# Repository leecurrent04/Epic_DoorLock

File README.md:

# EPIC Door Lock Project

## 1. 프로젝트 소개

연초고등학교 EPIC 동아리(2021~2022) 에서 교내 학생들의 자발적인 탐구 활동을 장려하기 위해 진행한 프로젝트 입니다.<br>
하드웨어 설계는 [KiCAD](https://www.kicad.org/) 를 사용하였고, 소프트웨어는 avr-gcc 컴파일러를 이용한 avr C 언어로 작성되었습니다.

<br>

## 2. 컴파일

Makefile을 이용하여 컴파일하는 경우, Makefile과 같은 위치에 `out` 폴더를 생성해야 합니다.

| 필요한 패키지 | 설명               |
| :-----------: | :----------------- |
|    avr-gcc    | 컴파일러           |
|   avr-libc    | 라이브러리         |
|   avr-size    | 메모리 사용량 확인 |
|    avrdude    | 업로더             |

<br>

### 1. in Linux

1. Set up (Debian)
    <br>
    패키지 설치는 Debian 기준으로 설명하고 있습니다. 자신의 환경에 맞추어 사용하시길 바랍니다.
    <br>

    ```console
    apt update && apt upgrade
    apt install avr-gcc avr-libc avr-size avrdude
    ```
    <br>

2. Download source code
    <br>
    ```console
    git clone https://github.com/leecurrent04/Epic_DoorLock
    cd ./Epic_DoorLock/ver3/code/avr/
    ```
    <br>

3. Set admin card
    <br>
    [main.c](https://github.com/leecurrent04/Epic_DoorLock/blob/main/ver3/code/avr/main.c) 파일의 16, 17줄을 편집하여 관리자 카드를 등록합니다.<br>
    RFID 카드의 4byte UID 코드를 1byte씩 기입합니다. 카드의 UID 코드는 [[NFC Tools - Google Play]](https://play.google.com/store/apps/details?id=com.wakdev.wdnfc&hl=en) 프로그램을 통하여 알 수 있습니다. (프로그램내 시리얼 번호 확인)<br>
    반드시 등록한 관리자 카드의 갯수에 맞게 `cardAdmin_Num` 값을 변경해주어야 합니다.
    <br>
    ```c
    #define cardAdmin_Num 2
    uint8_t cardAdmin_UID[cardAdmin_Num][4] = {
            {0x12, 0x34, 0x56, 0x78},
            {0x0A, 0x0B, 0x0C, 0x0D}
    };
    ```
    <br>

4. Complile
    <br>
    변경 사항을 저장한 후 아래 명령어를 이용하여 코드를 컴파일 합니다.
    <br>
    ```console
    mkdir out
    make all
    ```
    <br>또는 다음과 같은 명령어를 사용할 수 있습니다.<br>

    ```console
	avr-gcc -Wall -mmcu=atmega168p -Os main.c ./lib/* -o ./out/output.o
	avr-objcopy -j .text -j .data -O ihex ./out/output.o ./out/main.hex
    ```
    <br>

5. Upload
    <br>
    [Makefile](https://github.com/leecurrent04/Epic_DoorLock/blob/main/ver3/code/avr/Makefile) 의 2, 4, 5번째 줄을 환경에 맞게 편집합니다.<br>

    ```makefile
    PORT=/dev/ttyUSB0       # SET YOUR PORT
    OBJ_FILES=./lib/*
    BaudRate=115200         # SET BuadRate
    PROGRAMMER=arduino      # SET Programmer
    ```

    <br>아래의 명령어를 터미널에 입력하여 업로드 합니다.<br>

    ```console
    make flash
    ```

    <br>USBtinyISP를 사용하는 경우(권장), 다음의 명령어를 터미널에 입력하면 됩니다.<br>

    ```console
	avrdude -v -p m168p -c usbtiny -U flash:w:./out/main.hex:i
    ```

    <br><br>

### 2. Windows & Mac

[Microchip AVR GCC Compiler](https://www.microchip.com/en-us/tools-resources/develop/microchip-studio/gcc-compilers) 를 사용하여 Linux와 같은 과정을 따르거나, ATMEL Studio를 사용하십시오. <br>
자세한 과정은 『아트멜 스튜디오와 아두이노로 배우는 ATmega328 프로그래밍(허경용)』 도서를 참고하십시오.<br>
(이 프로젝트는 ATmega168p을 사용하였으므로, 업로드 과정에서 유의)
<br><br>

## 4. 참고 라이브러리

RFID 관련 AVR 라이브러리 : https://github.com/asif-mahmud/MIFARE-RFID-with-AVR

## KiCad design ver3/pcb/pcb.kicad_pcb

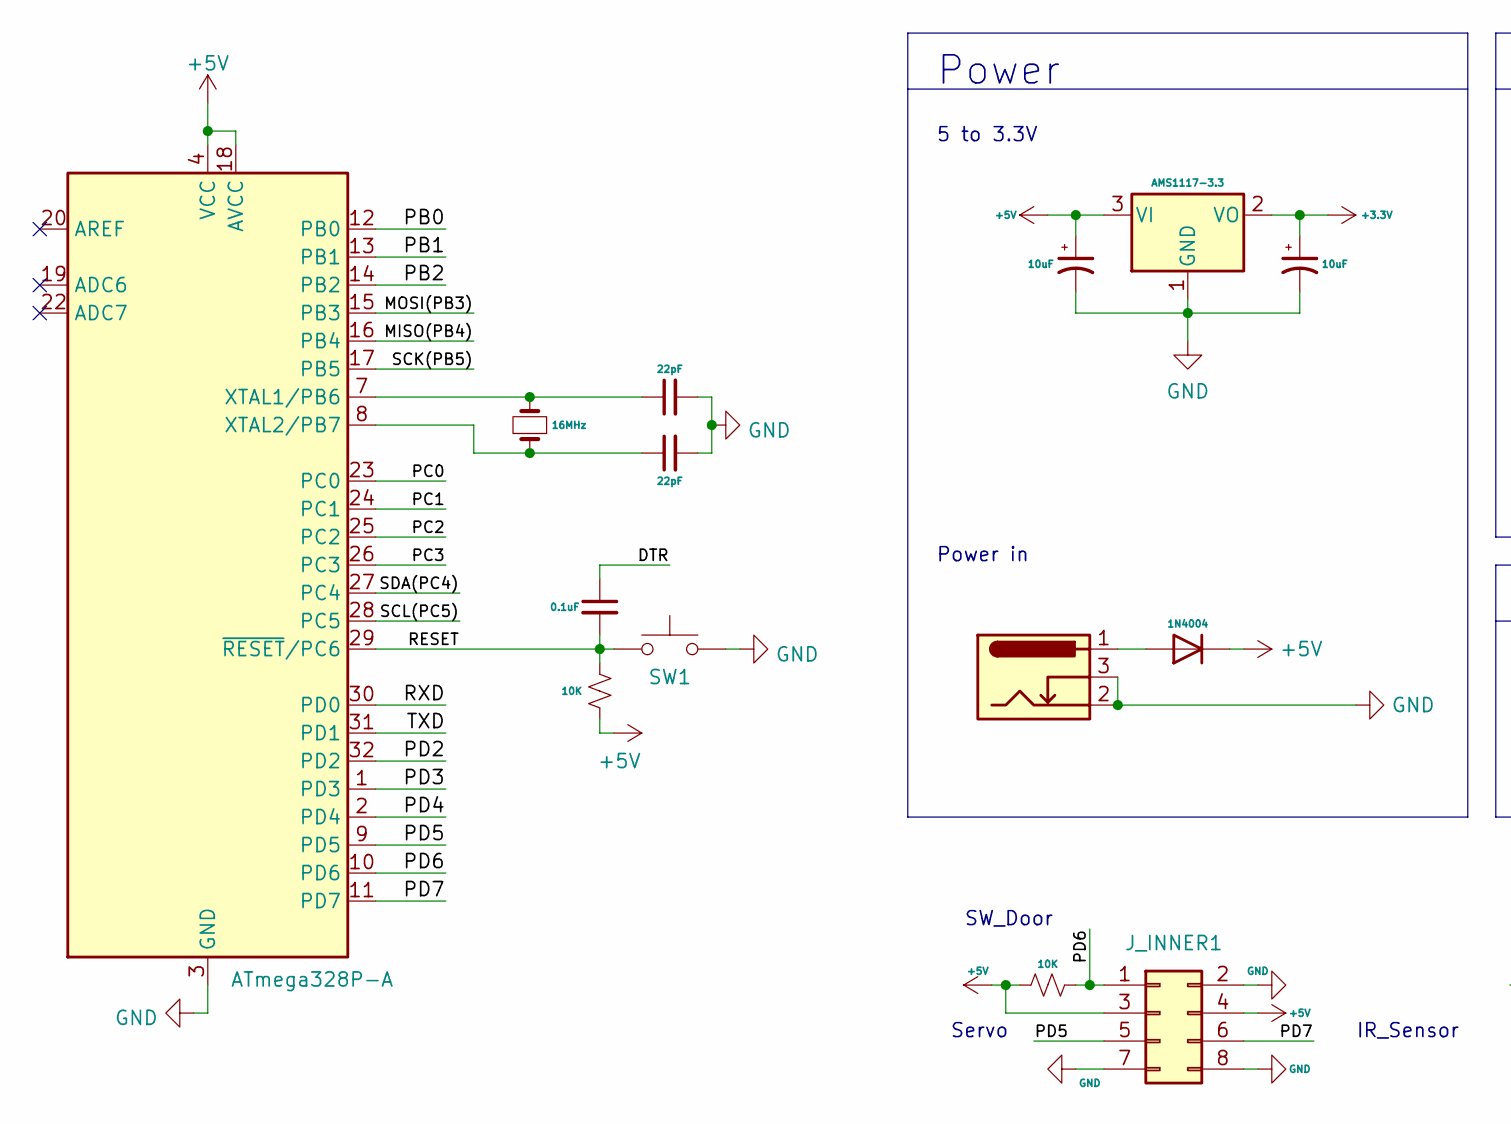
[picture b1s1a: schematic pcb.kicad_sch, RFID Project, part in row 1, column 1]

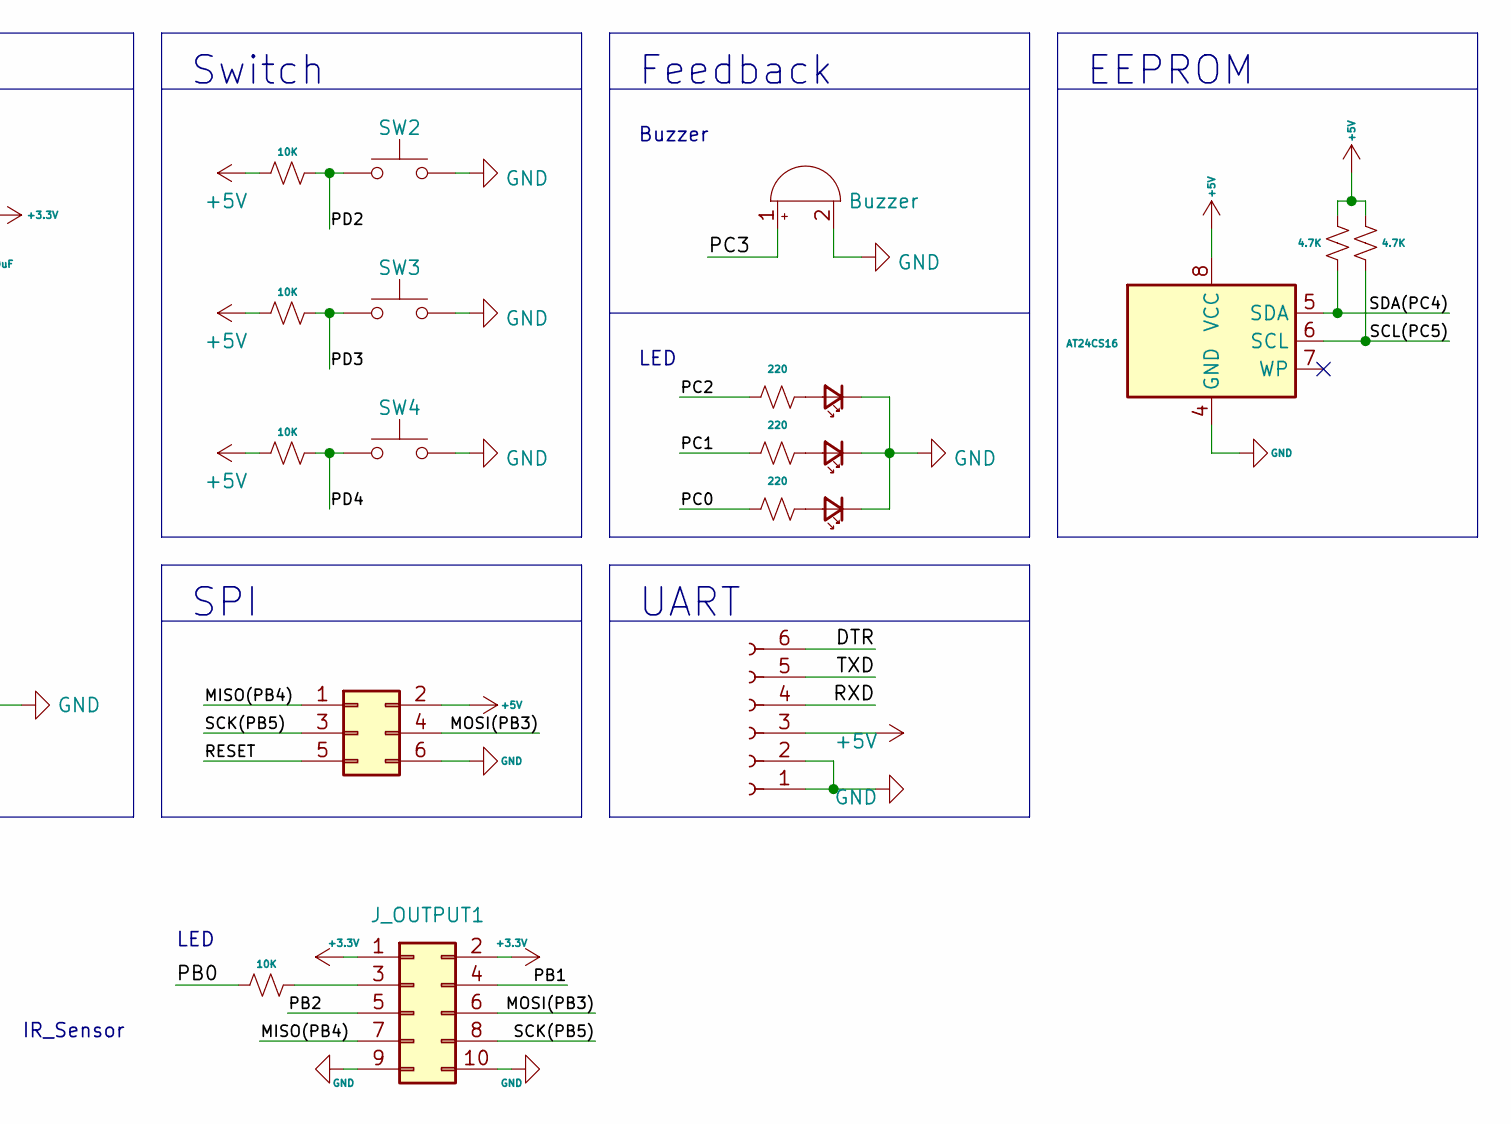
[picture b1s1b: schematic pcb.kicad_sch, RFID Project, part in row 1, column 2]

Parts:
BZ1: Buzzer; FQ-014[Buzzer]
C1: 0.1uF; C_0603_1608Metric
C2, C3: 22pF; C_0603_1608Metric
C4, C5: 10uF; CP_EIA-3216-10_Kemet-I
D1: 1N4004; D_SMA
D2, D3, D4: LED_Small; LED_0603_1608Metric
J_INNER1: Conn_02x04_Odd_Even; PinHeader_2x04_P2.54mm_Vertical
J_OUTPUT1: Conn_02x05_Odd_Even; PinHeader_2x05_P2.54mm_Vertical
J_SPI1: Conn_02x03_Odd_Even; PinHeader_2x03_P2.54mm_Vertical
J_UART1: Conn_01x06_Female; PinHeader_1x06_P2.54mm_Vertical
POWER_JACK1: 5.5pi; BarrelJack_Horizontal
R1, R2, R3, R4, R5, R6: 10K; R_0603_1608Metric
R7, R8, R9: 220; R_0603_1608Metric
R10, R11: 4.7K; R_0603_1608Metric
SW1: SW_Push; PinHeader_1x02_P2.54mm_Vertical
SW2: SW_Push; SW_PUSH-12mm
SW3, SW4: SW_Push; SW_PUSH_6mm_H5mm
U1: ATmega328P-A; TQFP-32_7x7mm_P0.8mm
U2: AMS1117-3.3; SOT-223-3_TabPin2
U3: AT24CS16; DIP-8_W7.62mm_Socket_LongPads
Y1: 16MHz; Crystal_HC49-4H_Vertical

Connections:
+3V3: C5.1, J_OUTPUT1.1, J_OUTPUT1.2, U2.2 (VO)
+5V: C4.1, D1.1 (K), J_INNER1.3, J_INNER1.4, J_SPI1.2, J_UART1.3, R1.1, R2.2, R4.1, R5.1, R6.1, R10.1, R11.1, U1.4 (VCC), U1.6 (VCC), U1.18 (AVCC), U2.3 (VI), U3.8 (VCC)
/DTR: C1.1, J_UART1.6
/MISO(PB4): J_OUTPUT1.7, J_SPI1.1, U1.16 (PB4)
/MOSI(PB3): J_OUTPUT1.6, J_SPI1.4, U1.15 (PB3)
/PB0: R3.1, U1.12 (PB0)
/PB1: J_OUTPUT1.4, U1.13 (PB1)
/PB2: J_OUTPUT1.5, U1.14 (PB2)
/PC0: R9.1, U1.23 (PC0)
/PC1: R8.1, U1.24 (PC1)
/PC2: R7.1, U1.25 (PC2)
/PC3: BZ1.1 (-), U1.26 (PC3)
/PD2: R4.2, SW2.1, U1.32 (PD2)
/PD3: R5.2, SW3.1, U1.1 (PD3)
/PD4: R6.2, SW4.1, U1.2 (PD4)
/PD5: J_INNER1.5, U1.9 (PD5)
/PD6: J_INNER1.1, R2.1, U1.10 (PD6)
/PD7: J_INNER1.6, U1.11 (PD7)
/RESET: C1.2, J_SPI1.5, R1.2, SW1.1, U1.29 (~RESET/PC6)
/RXD: J_UART1.4, U1.30 (PD0)
/SCK(PB5): J_OUTPUT1.8, J_SPI1.3, U1.17 (PB5)
/SCL(PC5): R11.2, U1.28 (PC5), U3.6 (SCL)
/SDA(PC4): R10.2, U1.27 (PC4), U3.5 (SDA)
/TXD: J_UART1.5, U1.31 (PD1)
GND: BZ1.2 (+), C2.2, C3.2, C4.2, C5.2, D2.1 (K), D3.1 (K), D4.1 (K), J_INNER1.2, J_INNER1.7, J_INNER1.8, J_OUTPUT1.9, J_OUTPUT1.10, J_SPI1.6, J_UART1.1, J_UART1.2, POWER_JACK1.2, POWER_JACK1.3, SW1.2, SW2.2, SW3.2, SW4.2, U1.3 (GND), U1.5 (GND), U1.21 (GND), U2.1 (GND), U3.4 (GND)
unnamed: C2.1, U1.7 (XTAL1/PB6), Y1.2
unnamed: C3.1, U1.8 (XTAL2/PB7), Y1.1
unnamed: D1.2 (A), POWER_JACK1.1
unnamed: D2.2 (A), R7.2
unnamed: D3.2 (A), R8.2
unnamed: D4.2 (A), R9.2
unnamed: J_OUTPUT1.3, R3.2

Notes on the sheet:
Feedback
Power in
Power
Servo
UART
Buzzer
IR_Sensor
LED
SW_Door
SPI
5 to 3.3V
EEPROM
Switch

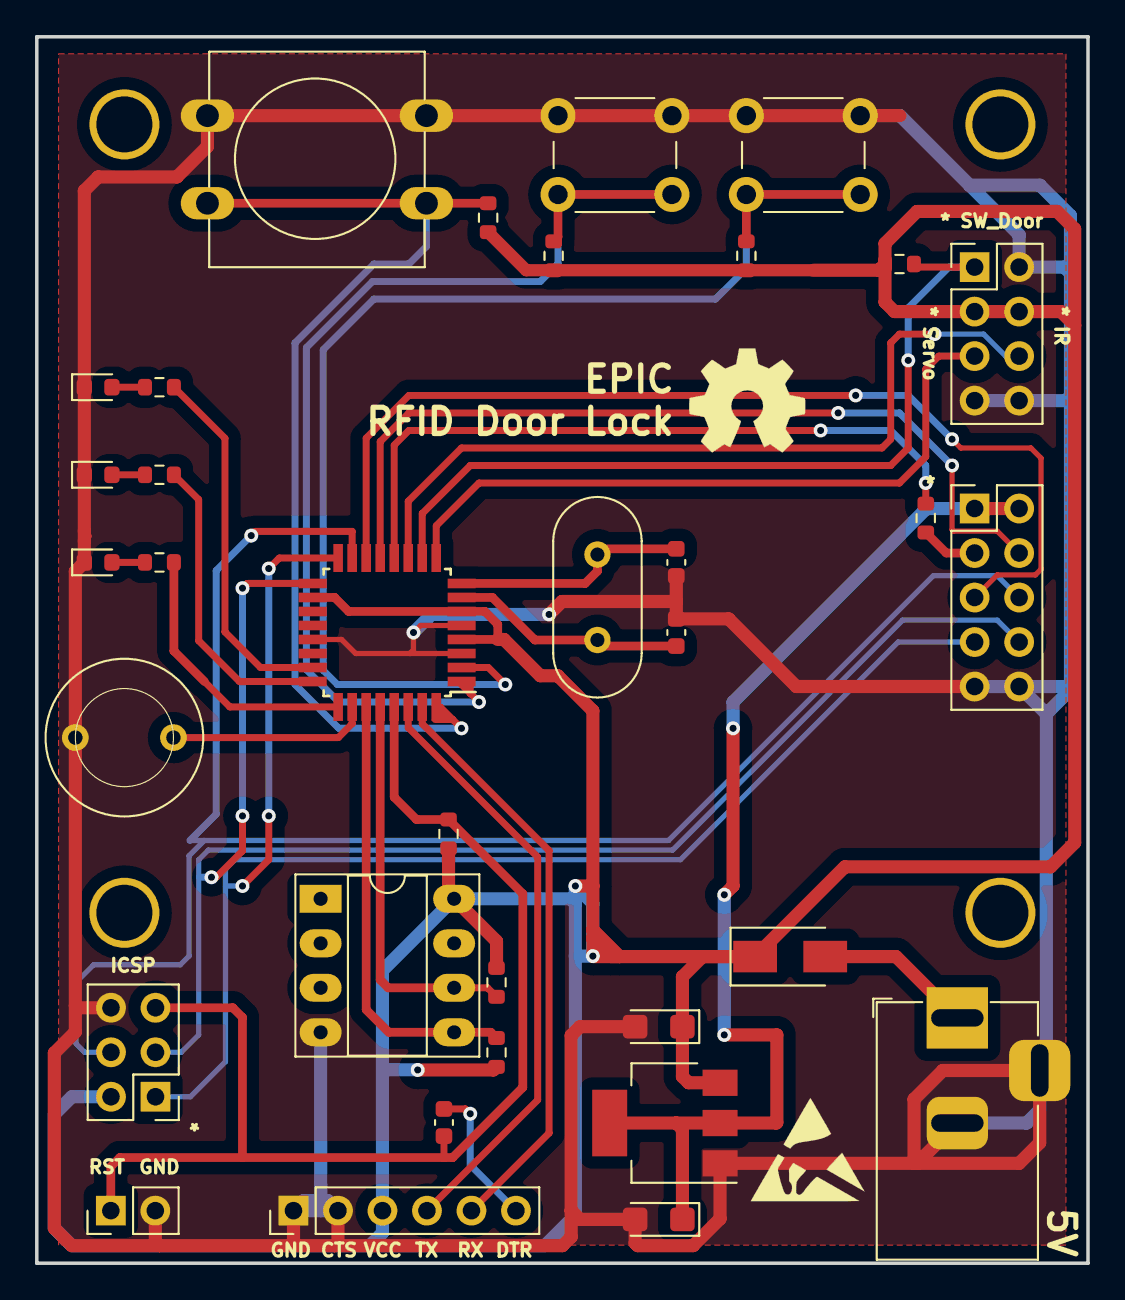
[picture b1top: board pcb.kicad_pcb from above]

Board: 2 copper layers, 60.0 x 70.0 mm, 40 parts (0 on the bottom side), 32 nets.

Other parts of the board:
HOLE1, HOLE2, HOLE3, HOLE4: (no value)
REF_ESD: ESD-Logo_6.6x6mm_SilkScreen
REF_OSHW: OSHW-Symbol_6.7x6mm_SilkScreen

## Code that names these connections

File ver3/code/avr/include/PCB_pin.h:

//
// Created by leecurrent04 on 22. 5. 13.
//

#ifndef AVR_PCB_PIN_H
#define AVR_PCB_PIN_H

#include "mfrc522.h"

#define LED_C0 0x01     // PC0
#define LED_C1 0x02     // PC1
#define LED_C2 0x04     // PC2
#define BUZZ_C3 0x08    // PC3
#define BTN_D2 0x04     // PD2
#define BTN_D3 0x08     // PD3
#define BTN_D4 0x10     // PD4
#define D_BTN_D6 0x40   // PD6
#define ServoPin 0x20   // PD5

#define BuzzerTime 500
#define BtnDTime 100

#define Servo_PulseNum 20

uint16_t card_Num;

uint8_t doorState;
uint8_t btnPressed;     // 버튼의 눌림 기록

// mfc522
uint8_t byte;
uint8_t str[MAX_LEN];

//Function
uint8_t checkRFID(uint8_t,uint16_t card_Num);
uint8_t readRFID(uint16_t *, uint16_t *, uint16_t *, uint16_t *);

void board_setup(void);
void beep_buzzer(void);
void doorOpen(void);
void doorClose(void);

unsigned char AT24C_write_byte(unsigned int,unsigned char);
unsigned char AT24C_read_byte(unsigned int addr);

#endif //AVR_PCB_PIN_H

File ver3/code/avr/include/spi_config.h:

/*
 * spi_config.h
 * 
 * Copyright 2013 Shimon <shimon@monistit.com>
 * 
 * This program is free software; you can redistribute it and/or modify
 * it under the terms of the GNU General Public License as published by
 * the Free Software Foundation; either version 2 of the License, or
 * (at your option) any later version.
 * 
 * This program is distributed in the hope that it will be useful,
 * but WITHOUT ANY WARRANTY; without even the implied warranty of
 * MERCHANTABILITY or FITNESS FOR A PARTICULAR PURPOSE.  See the
 * GNU General Public License for more details.
 * 
 * You should have received a copy of the GNU General Public License
 * along with this program; if not, write to the Free Software
 * Foundation, Inc., 51 Franklin Street, Fifth Floor, Boston,
 * MA 02110-1301, USA.
 * 
 * 
 */
#ifndef SPI_CONFIG_H
#define SPI_CONFIG_H

#include <avr/io.h>

/*
 * Set to 1, spi api will work in master mode
 * else in slave mode
 */
#define SPI_CONFIG_AS_MASTER 	1


/*
 * Config SPI pin diagram
 */
#define SPI_DDR		DDRB
#define SPI_PORT	PORTB
#define SPI_PIN		PINB

//#define SPI_MOSI	0x03
//#define SPI_MISO	0x04
//#define SPI_SS		0x02
//#define SPI_SCK		0x05

#define SPI_MOSI	PB3
#define SPI_MISO	PB4
#define SPI_SS		PB2
#define SPI_SCK		PB5

#endif

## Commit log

2022-06-19 0619
2022-06-19 0620
2022-07-19 0719
2022-09-28 2022.09.28 readme update
2023-03-31 2023.03.31 README update
2023-03-31 2023.03.31 memo.md udpate
2023-04-25 2023.04025
